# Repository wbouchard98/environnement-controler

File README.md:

# Projet environnement controlé
Collaborateurs : Simon Jourdenais (Symon4k18) et William Bouchard (wbouchard98)

Ce depôt contient les codes du projet de Serres Domestiques Automatisées, anciennement appelées Environnement Controlé.

Les dossier et fichiers intitulés 'UTest_' sont des tests unitaires.
Le dossier "Trash" contient plusieurs anciens code que nous avons pensés nécessaire, mais après restructuration de notre projet, avons abandonnés. Ces codes ne seront pas aussi bien expliqués et peuvent ne pas toujours fonctionner, mais nous avons décidé de les laisser là comme historique de notre travaille.
Le dossier "Project_Code" contient les codes nécessaires pour faire fonctionner la section logique du projet, tandis que le dossier "Project_EC_GUI" contient les codes nécessaires pour les programmes visuels. Plusieurs version sont disponible montrant l'évolution de notre travaille. Seulement la dernière version est conseillé d'être utilisée.

Le projet suivant sert à prendre des mesures de température, d'humidité et de qualité de l'air, par le biais de différents capteurs et de par la suite
réguler l'environnement.

Voici la liste de matériel utilisé pour le projet:
	1) RaspberryPi 4
	2) PCB "Bloc de capteurs" *
	3) PCB "Bloc de contrôle" *
	4) DS18B20 x2
	5) CSS811
	6) SEN0227
	7) Écran LCD tactile 7 pouces
	8) Bloc d'alimentation d'ordinateur 450 watts

	*Les détails des PCB seront montré plus loin.

Pour que le RaspberryPi fonctionne pour ce projet, voici les étapes que nous avons effectué:

# Étapes de l’installation de l’image du Raspberry Pi 

1)	Allez chercher une image de Raspberry Pi Buster Desktop 
2)	”Flash” une carte SD d’au moins 8Go avec cette image. Nous avons utilisé Balena Etcher pour cette étape.
3)	Faire la configuration du Raspberry Pi lors de son premier démarrage. Lorsqu’il vous est demandé de redémarrer le Raspberry Pi, redémarrer le.
4)	Maintenant, il faut activer les interfaces dont on aura besoin. Ouvrez un terminal, et tapez la commande : sudo raspi-config
5)	Une fois la fenêtre de configuration ouverte sélectionner l’index 5(Interfacing Options).
6)	Activer ‘’SSH’’, ‘’VNC’’, ‘’I2C’’ et ‘’1-Wire’’. Il faut aussi activer le ‘’Serial’’. Cependant lorsqu’il va être demandé s’il est désiré que le ‘’login shell’’ soit accessible depuis le serial, faire non, et lorsque l’usager est demandé de vouloir activer le ‘’Serial port hardware’’ faire oui.
7)	Redémarrez le Raspberry Pi pour effectuer les changements.
8)	Maintenant, il faut se connecter au serveur de temps pour pouvoir automatiquement mettre à jour le temps du Raspberry Pi. Ouvrez le fichier /etc/systemd/timesyncd.conf .
9)	Modifiez les lignes ‘’NTP’’ et ‘’FallbackNTP’’ pour que leur valeur sois : time.apple.com .
10)	Effectuez un : sudo systemctl restart systemd-timesync.service .
11)	Effectuer par la suite : sudo systemctl daemon-reload .
12)	Maintenant faire les ‘’update’’ et ‘’upgrade’’.
13)	Si vous utilisez un écran de petite taille, comme un écran 7" comme nous, nous vous recommandons de changer la résolution de l'écran. Pour ce faire, cliquer le logo Raspberry dans le haut de l'écran, puis aller sur "Preferences" et "Raspberry Pi Configuration". Aller dans l'onglet "Display" et puis "Set Resolution...". Nous utilisons "DMT mode 9 800x600 60Hz 4:3".

Une fois le RaspberryPi bien configuré, il faut ajouter les bonnes librairies pythons dans le RaspberryPi pour que les codes puissent bien fonctionner.

Voici les démarches à suivre pour l'installation de ces librairies:

# Étapes pour l’installation des librairies Python

1) Premièrement, il faut s’assurer que Pyhton3 soit bien installé : sudo apt-get install python3 .
2) Une fois installé, il faut pouvoir accéder au I/O du Raspberry Pi. La librairie suivante va faire ce travail : sudo pip3 install RPI.GPIO
3) Pour pouvoir lire les données du capteur SEN0227 qui va lire la température de l’environnement dans lequel le Raspberry Pi se situe (et non l’environnement que l’on souhaite contrôler) : sudo pip3 install sht20 .
4) Maintenant, pour être capable de faire les communications MQTT, il nous faut un "Broker MQTT" : sudo apt-get install mosquitto : et : sudo apt-get install mosquitto-clients .
5) Une fois le "Broker" installé, il nous faut la librairie pour accéder à ce "Broker" : sudo pip3 install paho-mqtt .
6) Maintenant, il faut que notre "GUI" puisse accéder aux librairies PYQT5 : sudo apt-get install qt5-default pyqt5-dev pyqt5-dev-tools
7) Pour contrôler la plupart des éléments de l’environnement, l’utilisation d’un PID est importante. La librairie suivante va nous permettre d’utiliser des PID : sudo pip3 install simple-pid .

Maintenant il est temps d'ajouter les librairies à l'IDE Arduino:

# Étape pour l’installation des librairies Arduino

1) Adafruit_CCS811: Pour l'ajouter à l'IDE Arduino, ouvrir l'IDE Arduino, cliquer sur l'onglet "Croquis". Aller par la suite sur "Inclure une bibliothèque" et ensuite "Gérer les bibliothèques". Taper "CCS" dans la barre de recherche et une librairie du nom de "Adafruit CSS811 Library par Adafruit" devrait être disponible. Cliquer sur "Installer".  

2) DFRobot_SHT20: Pour ajouter cette librairie, visiter DFRobot/DFRobot_SHT20 (github.com) . Télécharger le repositary avec le bouton vert avec la flèche. Une fois télécharger mettre le dossier "DFRobot_SHT20-master" dans le dossier "C:\Program Files (x86)\Arduino\libraries". 

3) OneWire: Suivre les étapes pour le Adafruit_CCS811, mais taper "Onewire" dans la barre de recherche. Dans le "ComboBox" "Sujet" sélectionner "Communication". Une librairie du nom de "OneWire" devrait être disponible. Installer celle-ci. 

4) DallasTemperature: Suivre les étapes pour le Adafruit_CCS811, mais tapper "Dallas" dans la barre de recherche. Une librairie du nom de "DallasTemperature" devrait être        disponible. Installer celle-ci. 

## Explication des PCB

Notre projet contient deux PCB. L'un d'entre eux sert à la lecture des capteurs, et l'autre sert à contrôler les diverts éléments de contrôle.
### PCB bloc de capteurs

Pour lire l'état actuel de la chambre, nous avons créé un PCB qui relie plusieurs capteurs(DS18B20, SEN0227, CCS811) à un ATmega328p-AU. Les informations des capteurs sont ensuites transmises au RaspberryPi.
#### Transmission des informations
Nous utilisons la prise USB-mini pour transmettre les informations des capteurs vers le RaspberryPi. Ce même connecteur peut être utilisé pour le transfert du code .ino/.c. Nous avons aussi mis des traces pour un connecteur pour le module bluetooth HM-10.
Pour changer le mode entre Bluetooth et USB, il suffit de changer la position du cavalier JP201 et JP203 (position 1-2 Bluetooth, 2-3 USB). 
Dans notre projet nous utilisons pas le module Bluetooth, alors aucun code n'a été fait pour son utilisation, mais son ajout peut être possible grâce au PCB.
#### Alimentation
L'alimentation de ce PCB vient du câble USB, mais si on désire utiliser le module Bluetooth, alors un connecteur(J202) permet de connecter une batterie Li-po de 5V pour alimenter le montage de façon indépendante au RaspberryPi.
Comme mentionné plus tôt, nous utilisons la communication USB, alors l'alimentation provenant de batterie Li-po n'a pas été testé.
#### Communication des capteurs
##### DS18B20
Le capteur de température DS18B20 communique avec le ATmega en protocole 1-wire. La plaque contient une empreinte pour placer directement un DS18B20 en format TO-92, et un connecteur permet de pouvoir aussi utiliser un DS18B20.
##### SEN0227
Le capteur de température/humidité SEN0227 communique en I2C avec le ATmega. La plaque contient une empreinte pour placer directement un SHT-20, et un connecteur permet de pouvoir aussi utiliser un SEN0227.
##### CCS811
Le capteur de qualité de l'air CCS811 communique en I2C avec le ATmega. La plaque contient les empreintes pour placer directement CCS811 et les composants requis pour son fonctionement, et un connecteur permet de pouvoir aussi utiliser un CCS811 de Keyestudio.
La trace JP301 permet de changer l'adresse du CCS811.
##### SGP30
Le capteur de qualité de l'air SGP30 communique en I2C avec le Atmega. La plaque contient une empreinte pour placer directement un SGP30, et un connecteur permet de pouvoir aussi utiliser un "board" SGP30 de Adafruit.
Dans notre projet nous utilisons pas le SGP30, alors aucun code dans notre conteneur Github sera fait avec la considération de son utilisation, mais il sera possible de modifier le code pour l'inclure s'il est désiré.

### PCB de contrôle

Ce PCB sert à transformer les PWM du RaspberryPi, pour qu'ils soient capable de contrôler les éléments de contrôle(Lumière, ventillation, chauffage, humidificateur).

#### Connection au RaspberryPi
Le RaspberryPi se connecte au PCB par l'entremise d'un câble plat 40 pins.
#### Ventillation
La ventillation est contrôllé par le GPIO-27 du RaspberryPi. Le signal du GPIO-27 est ensuite transformer en 120 VAC par un CPC1966B pour faire fonctionner le système de ventillation.

#### Élément chauffant
Même méthode que pour la ventillation, mais le GPIO-17 est utilisé.

#### Lumière
Même principle que la ventillation, mais le GPIO-06 est utilisé.

#### Déshumidificateur
Même principle que la ventillation, mais le GPIO-22 est utilisé. On a pas intégré le déshumidificateur à notre projet, alors notre code ne contient pas son activation, mais il est possible d'ajouter son activation si désiré.

#### Humidificateur
L'humidificateur est contrôlé par le GPIO-05 du RaspberryPi. Un CPC1907B transforme le signal du RaspberryPi en signal 24V.

#### LED 100W
Une LED de 100W peut être connecté au PCB pour utiliser au lieu du panneau de lumière. Cette lumière sera contrôlé par le GPIO-13 du RaspberryPi. Un transitor permet de faire circuler le courant pour allumer la LED.

#### Ventillation du boitier
Un ventillateur à l'intérieur du boitier permet de refroidir la température de celui-ci. Ce ventillateur est contrôllé par un PWM de la pin GPIO-12 du RaspberryPi. Un transitor permet de conduire le courant à partir du 12V.

#### Ventillateur de la LED 100W
Un ventillateur qui permet de refroidir la LED de 100W. Ce ventillateur est "driver" par un transitor contrôlé par la pin GPIO-18 du RaspberryPi.

#### Connecteur 12V supplémentaire
On ajouté ce connecteur pour pouvoir ajouter d'autre élément fonctionnant sur du 12V. Comme par exemple une pompe à eau pour arroser la terre ou un ventillaeur supplémentaire. Ce connecteur sera contrôler par la pin GPIO-19 du RaspberryPi.

## Utilisation de l'interface graphique
L'interface graphique se compose de deux sections: un menu ancré sur la gauche de l'écran et l'affichage principale qui occupe le restant. Voir figure ci-dessus.

Le menu nous permet de naviguer entre 4 modes de GUI différents. Le premier est le mode monitorage, le deuxième est le mode consigne, le troisième est le mode paramètre et finalement le dernier est le mode administrateur.

### Mode Monitorage
Le mode monitorage est bien simple; il affiche les valeurs reçues. Les valeurs sont la température, l'humidité, la concentration de C02 et la quantité de matière organique dans l'air. Voir la figure ci-dessus pour exemple de l'affichage en mode monitorage.

### Mode Consigne
Le mode consigne permet à l'usager d'accomplir plusieurs tâches. Premièrement, une section de l'affichage est réservé à afficher les valeurs de consignes courantes. Une autre section sert à modifier manuellement les valeurs des consignes courantes. Les valeurs à l'écran dans la section de l'affichage des consignes vont changer avec les modifications effectué. L'autre section sert à choisir ou enregistrer des valeurs de consignes. Ces valeurs sont alors réutilisables si l'usager souhaite les utiliser plus tard, ou si le système est mis hors tension. Voir la figure ci-dessus pour un visuel du GUI en mode consigne. Il est aussi possible d'ouvrir une autre fenêtre qui va permettre le contrôle des lumières.

#### Mode éclairage
Appelé à partir de la fenêtre consigne, permet de configurer un cycle d'activation et de désactivation des lumières.

### Mode Paramètre
Le mode paramètre nous permet de se connecter à la base de données ThingSpeak, de se connecter à un réseau Wi-Fi et à voir des informations utiles pour l'usgaer. Pour pouvoir entrer les informations requises de Thingspeak et du Wi-Fi, un clavier sera nécessaire. Simplement le brancher dans un port USB du RaspberryPi. L'iamge ci-dessous nous permet de voir un exemple de la fenêtre paramètre.

### Mode Administrateur
Le mode Administarteur permet de contrôler manuellement les éléments de contrôle. Cette fenêtre est très utile pour vérifier le fonctionnment de son matériel. Des "sliders" servent à ajuster le PWM des éléments et ainsi dicter leur intensité de fonctionnment. Voir la figure ci-dessus pour un apperçu.

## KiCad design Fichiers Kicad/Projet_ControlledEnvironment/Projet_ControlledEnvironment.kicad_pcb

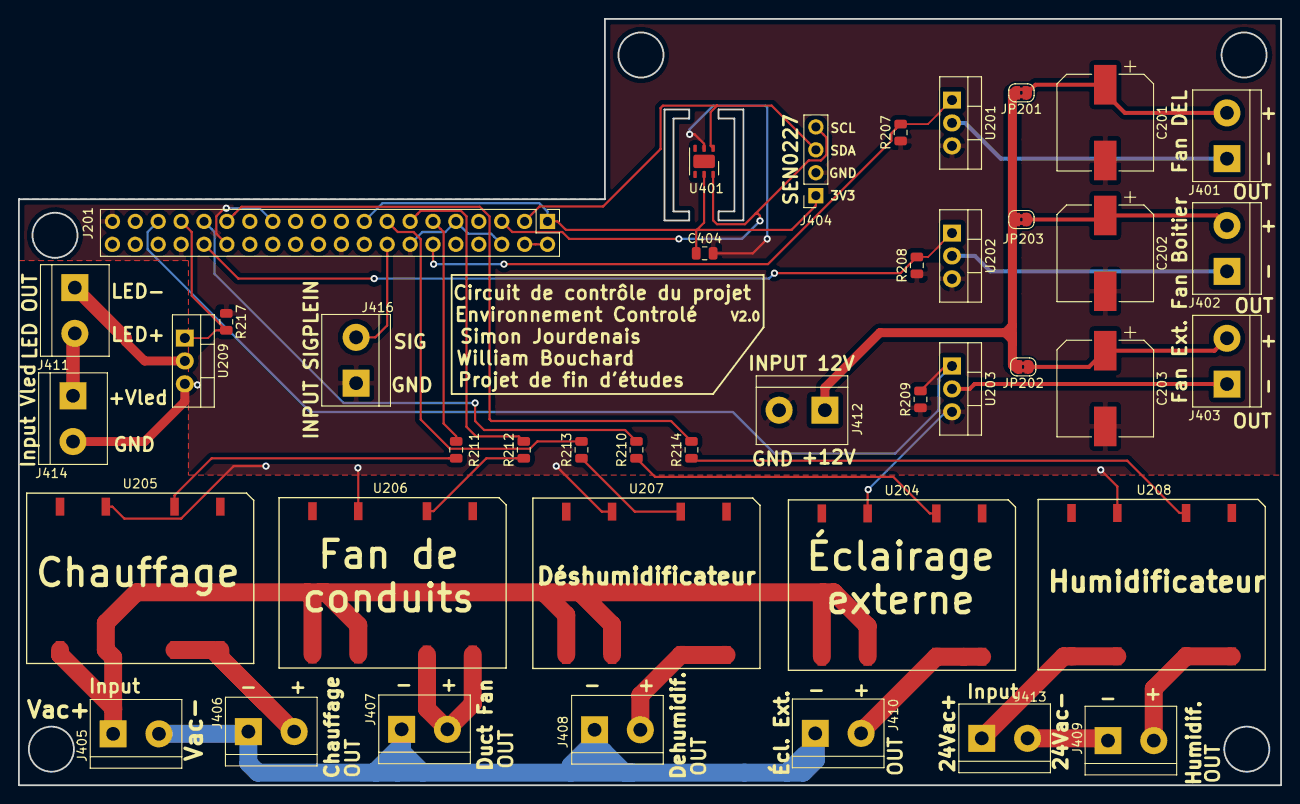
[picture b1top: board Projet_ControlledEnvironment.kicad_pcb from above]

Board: 2 copper layers, 140.0 x 85.0 mm, 42 parts (0 on the bottom side), 38 nets.

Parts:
C201, C202, C203: 470 uF; CP_Elec_10x10.5
C404: 0.1 uF; C_0805_2012Metric
J201: Pi 40-Pin Connector; PinHeader_2x20_P2.54mm_Vertical
J401, J402, J403, J405, J406, J407, J408, J409, J410, J411, J412, J413, J414, J416: Conn_01x02; TerminalBlock_bornier-2_P5.08mm
J404: Conn_01x04; PinSocket_1x04_P2.54mm_Vertical
JP201, JP202, JP203: SolderJumper_2_Bridged; SolderJumper-2_P1.3mm_Bridged2Bar_RoundedPad1.0x1.5mm
R207, R208, R209, R217: 10k; R_0805_2012Metric
R210, R211, R212, R213, R214: 420; R_0805_2012Metric
U201, U202, U203, U209: FQP30N06L; TO-220-3_Vertical
U204, U205, U206, U207: CPC1966B; PSOIC-8
U208: CPC1907B; PSOIC-8
U401: SHT2x; DFN-6-1EP_3x3mm_P1mm_EP1.5x2.4mm

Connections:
24VAC+: J413.1, U208.5, U208.6
24VAC-: J409.1, J413.2
100W_LED+: J411.2, J414.1
100W_LED-: J411.1, U209.2
+3V3: C404.1, J201.1, J201.17, J404.1, U401.5
+5V: J201.2, J201.4
+12V: J412.1, JP201.2, JP202.2, JP203.2
/Mainblock Core/GPIO5: J201.29, R214.2
/Mainblock Core/GPIO6: J201.31, R210.2
/Mainblock Core/GPIO12: J201.32, R208.2, U202.1
/Mainblock Core/GPIO13: J201.33, R217.2, U209.1
/Mainblock Core/GPIO17: J201.11, R211.2
/Mainblock Core/GPIO18: J201.12, R207.2, U201.1
/Mainblock Core/GPIO19: J201.35, R209.2, U203.1
/Mainblock Core/GPIO22: J201.15, R213.2
/Mainblock Core/GPIO27: J201.13, R212.2
BOITIER_FAN_IN: C202.1, J402.2, JP203.1
BOITIER_FAN_OUT: J402.1, U202.2
Dehumidificateur: J408.2, U207.7, U207.8
DuctFan: J407.2, U206.7, U206.8
EXT_OPT_FAN_IN: C203.1, J403.2, JP202.1
EXT_OPT_FAN_OUT: J403.1, U203.2
Ext_Light: J410.2, U204.7, U204.8
GND: C201.2, C202.2, C203.2, C404.2, J201.6, J201.9, J201.14, J201.20, J201.25, J201.30, J201.34, J201.39, J404.2, J412.2, J414.2, J416.1, R207.1, R208.1, R209.1, R217.1, U201.3, U202.3, U203.3, U204.3, U205.3, U206.3, U207.3, U208.3, U209.3, U401.2
GPIO23_SIGPLEIN: J201.16, J416.2
Heater: J406.2, U205.7, U205.8
Humidificateur: J409.2, U208.7, U208.8
LED_FAN_IN: C201.1, J401.2, JP201.1
LED_FAN_OUT: J401.1, U201.2
unnamed: R210.1, U204.2
unnamed: R211.1, U205.2
unnamed: R212.1, U206.2
unnamed: R213.1, U207.2
unnamed: R214.1, U208.2
SCL_PI: J201.5, J404.4, U401.6
SDA_PI: J201.3, J404.3, U401.1
VAC+: J405.1, U204.5, U204.6, U205.5, U205.6, U206.5, U206.6, U207.5, U207.6
VAC-: J405.2, J406.1, J407.1, J408.1, J410.1

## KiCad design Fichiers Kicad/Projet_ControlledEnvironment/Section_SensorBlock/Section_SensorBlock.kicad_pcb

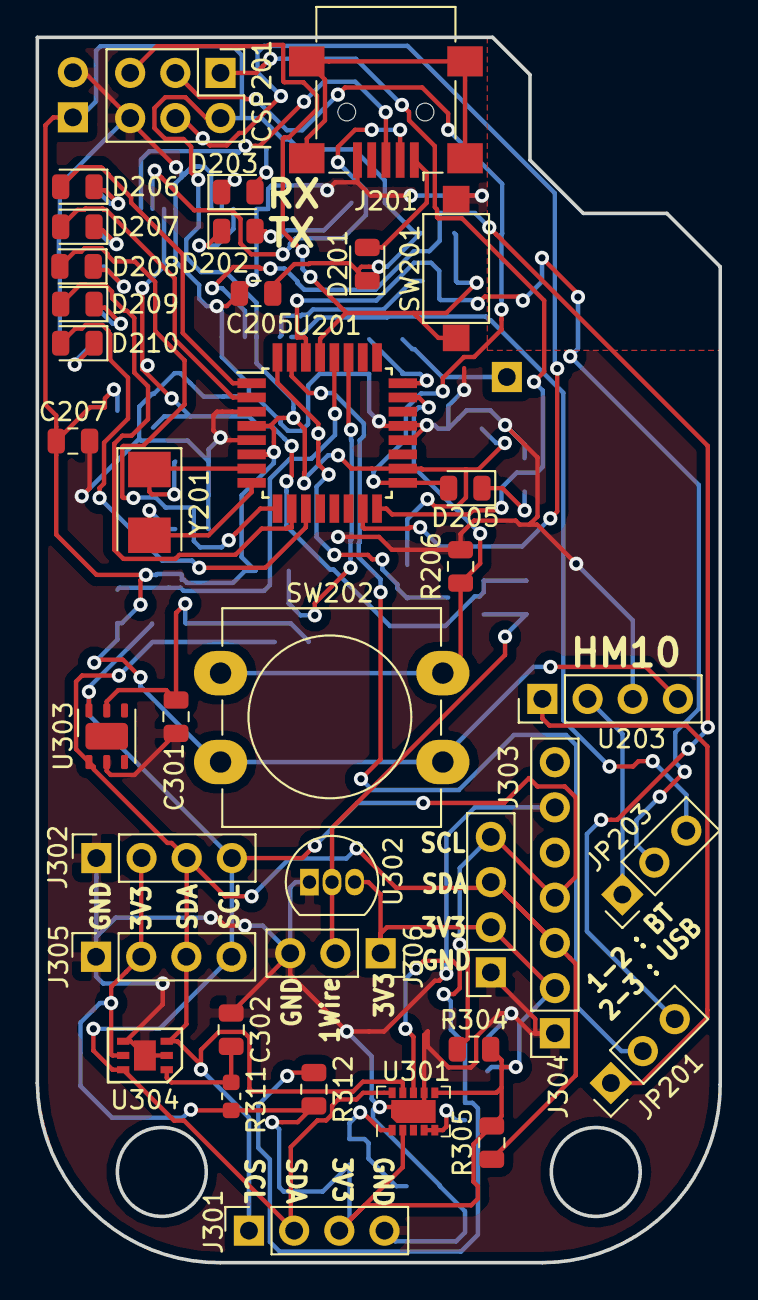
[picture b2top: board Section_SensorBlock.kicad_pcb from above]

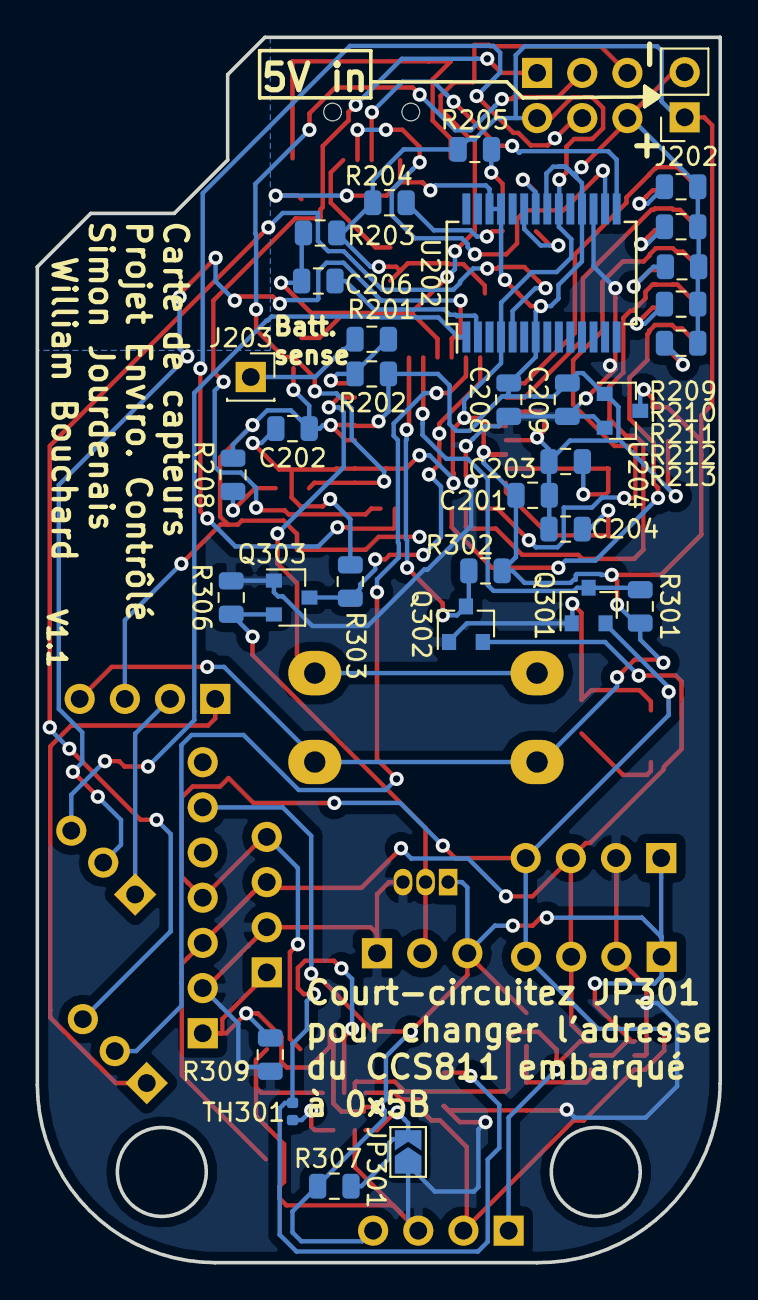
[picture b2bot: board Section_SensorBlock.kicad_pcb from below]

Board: 2 copper layers, 38.4 x 68.9 mm, 70 parts (33 on the bottom side), 47 nets.

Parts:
C201, C202, C205, C206, C208, C301, C302: 0.1 uF; C_0805_2012Metric
C203, C204: 18 pF; C_0805_2012Metric
C207: 1 uF; C_0805_2012Metric
C209: 10 uF; C_0805_2012Metric
D201: D_Schottky; D_0805_2012Metric
D202: LED_RED_TX; LED_0805_2012Metric
D203: LED_BLUE_RX; LED_0805_2012Metric
D205: LED_YLW_USR; LED_0805_2012Metric
D206: LED_RED; LED_0805_2012Metric
D207, D208: LED_YLW; LED_0805_2012Metric
D209, D210: LED_GRN; LED_0805_2012Metric
ICSP201: Conn_02x03; PinHeader_2x03_P2.54mm_Vertical
J201: USB_B_Mini; USB_Mini-B_Lumberg_2486_01_Horizontal
J202: Conn_01x02_Female; PinSocket_1x02_P2.54mm_Vertical
J203: Sense_Batt; PinSocket_1x01_P2.54mm_Vertical
J301: Conn_OLED_Screen; PinSocket_1x04_P2.54mm_Vertical
J302: Conn_01x04; PinSocket_1x04_P2.54mm_Vertical
J303: Conn_QT_CCS; PinSocket_1x04_P2.54mm_Vertical
J304: Conn_Keyes_CCS; PinSocket_1x07_P2.54mm_Vertical
J305: Conn_QT_SGP30; PinSocket_1x04_P2.54mm_Vertical
J306: Conn_01x03; PinSocket_1x03_P2.54mm_Vertical
JP201, JP203: Jumper_NC_Dual; PinHeader_1x03_P2.54mm_Vertical
JP301: Jumper_Address_I2C; SolderJumper-2_P1.3mm_Open_TrianglePad1.0x1.5mm
Q301, Q302, Q303: BSS138; SOT-23
R201: 90k; R_0805_2012Metric
R202, R203, R301, R302, R303, R304, R305, R306, R307, R309: 10k; R_0805_2012Metric
R204, R205, R208, R209, R210, R211, R212, R213: 330; R_0805_2012Metric
R206: 4.7k; R_0805_2012Metric
R311: 4.7 Ohms; R_0603_1608Metric
R312: 100k; R_0805_2012Metric
SW201: Reset; SW_SPST_CK_RS282G05A3
SW202: SW_Push; SW_PUSH-12mm_Wuerth-430476085716
TH301: 10k; R_0402_1005Metric
U201: ATmega328P-AU; TQFP-32_7x7mm_P0.8mm
U202: FT232RL; SSOP-28_5.3x10.2mm_P0.65mm
U203: HM10; PinHeader_1x04_P2.54mm_Vertical
U204: AP2210-3.3; SOT-23
U301: CCS811; AMS_LGA-10-1EP_2.7x4mm_P0.6mm
U302: DS18B20; TO-92_Inline
U303: SHT2x; DFN-6-1EP_3x3mm_P1mm_EP1.5x2.4mm
U304: SGP30; DFN-7
Y201: 16 MHz; Crystal_SMD_5032-2Pin_5.0x3.2mm

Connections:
+3V3: C208.1, C209.1, C301.1, J301.3, J302.2, J303.2, J304.2, J305.2, J306.1, JP301.1, Q301.1, Q302.1, Q303.1, R304.2, R305.2, R306.2, R309.2, R311.1, R312.2, U202.17, U204.2, U301.2, U301.6, U302.3, U303.5, U304.5
+5V: C201.2, C202.2, C205.2, C207.1, D201.1, ICSP201.2, J202.1, R203.1, R204.2, R205.1, R301.2, R302.2, R303.2, SW202.1, U201.4, U201.6, U201.18, U202.4, U202.20, U203.4, U204.3
/Sensorblock MCU sheet/BTN_In: R206.1, SW202.2, U201.23
/Sensorblock MCU sheet/BT_RX: JP201.1, U203.1
/Sensorblock MCU sheet/BT_TX: JP203.1, U203.2
/Sensorblock MCU sheet/DTR: C206.1, U202.2
/Sensorblock MCU sheet/LED_Meter_1: D206.2, U201.1
/Sensorblock MCU sheet/LED_Meter_2: D207.2, U201.2
/Sensorblock MCU sheet/LED_Meter_3: D208.2, U201.9
/Sensorblock MCU sheet/LED_Meter_4: D209.2, U201.10
/Sensorblock MCU sheet/LED_Meter_5: D210.2, U201.11
/Sensorblock MCU sheet/PB3-MOSI: ICSP201.4, U201.15
/Sensorblock MCU sheet/PB4-MISO: ICSP201.1, U201.16
/Sensorblock MCU sheet/PB5-SCK: D205.2, ICSP201.3, U201.17
/Sensorblock MCU sheet/PC6-RST: C206.2, ICSP201.5, R203.2, SW201.1, U201.29
/Sensorblock MCU sheet/RX_ARD: JP203.2, U201.30
/Sensorblock MCU sheet/TX_ARD: JP201.2, U201.31
/Sensorblock MCU sheet/USB_RX: JP201.3, U202.5
/Sensorblock MCU sheet/USB_TX: JP203.3, U202.1
/Sensorblock sensor sheet/1Wire_3V3: J306.2, Q303.2, R306.1, U302.2
/Sensorblock sensor sheet/SCL_3V3: J301.2, J302.4, J303.4, J304.4, J305.4, Q301.2, R304.1, U301.10, U303.6, U304.6
/Sensorblock sensor sheet/SDA_3V3: J301.1, J302.3, J303.3, J304.3, J305.3, Q302.2, R305.1, U301.9, U303.1, U304.3
AT_1Wire: Q303.3, R303.1, U201.32
AT_SCL: Q301.3, R301.1, U201.28
AT_SDA: Q302.3, R302.1, U201.27
GND: C201.1, C202.1, C203.1, C204.1, C205.1, C207.2, C208.2, C209.2, C301.2, C302.1, ICSP201.6, J201.5, J202.2, J301.4, J302.1, J303.1, J304.1, J304.6, J305.1, J306.3, R202.2, R206.2, R208.2, R209.2, R210.2, R211.2, R212.2, R213.2, R307.1, R309.1, SW201.2, U201.3, U201.5, U201.20, U201.21, U202.7, U202.18, U202.21, U202.25, U202.26, U203.3, U204.1, U301.7, U301.11, U302.1, U303.2, U304.2, U304.4, U304.7
unnamed: C203.2, U201.7, Y201.1
unnamed: C204.2, U201.8, Y201.2
unnamed: C302.2, R311.2, U304.1
unnamed: D201.2, J201.1
unnamed: D202.1, U202.23
unnamed: D202.2, R204.1
unnamed: D203.1, U202.22
unnamed: D203.2, R205.2
unnamed: D205.1, R208.1
unnamed: D206.1, R209.1
unnamed: D207.1, R210.1
unnamed: D208.1, R211.1
unnamed: D209.1, R212.1
unnamed: D210.1, R213.1
unnamed: J201.2, U202.16
unnamed: J201.3, U202.15
unnamed: J203.1, R201.1
unnamed: JP301.2, R307.2, U301.1
unnamed: R201.2, R202.1, U201.24
unnamed: R312.1, TH301.2, U301.8
unnamed: TH301.1, U301.4, U301.5

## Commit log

2021-01-26 Creation du repos et ajout d'un script de test
2021-01-26 Creation du README
    Information très brève. À compléter.
2021-01-26 Deplacement du fichier testGPIO dans un folder associer
2021-01-27 Addition du test on_off
2021-01-27 modif du info_test
2021-02-14 Ajout du code de test pour le capteur de CO2
2021-02-15 Rename info_test to Read_me.md
2021-02-15 Modification de structure et push de tests unitaires
2021-02-16 Ajout du programme de lecture des 3 capteurs et d'ecriture influx
2021-03-05 Thingspeak code complet
2021-03-05 Ajout du code pour thingspeak
2021-03-15 Ajout de code du GUI avec le code de lecture
2021-03-16 Code Nano PID, Soil, SHT and CCS in one
2021-03-29 Ajout du Ui de la fenetre de controle
2021-03-29 ajout de mqttbuttontest3.ui a partir du nouveau pi
2021-03-29 Ajout de code plus a jour
2021-04-12 Fichier Kicad ajoutés
2021-04-30 GUI Added et Modif Kicad
2021-05-02 GUI Final
2021-05-02 Reorganisation
2021-05-18 Final Code
